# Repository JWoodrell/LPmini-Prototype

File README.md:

# LPmini-Prototype

v1.4b - Fixed a few errors in 1.4, changed jumper section to reflect FR5994 launchpad config

v1.4 - MSP430FR5994 board, onboard debugger

v1.3 - thin form 0.5" wide BGA package

v1.2 - added combo castillations and shrunk width

v1.1 - added TItan logo to back of board and a few small changes

v1.0 - initial board version

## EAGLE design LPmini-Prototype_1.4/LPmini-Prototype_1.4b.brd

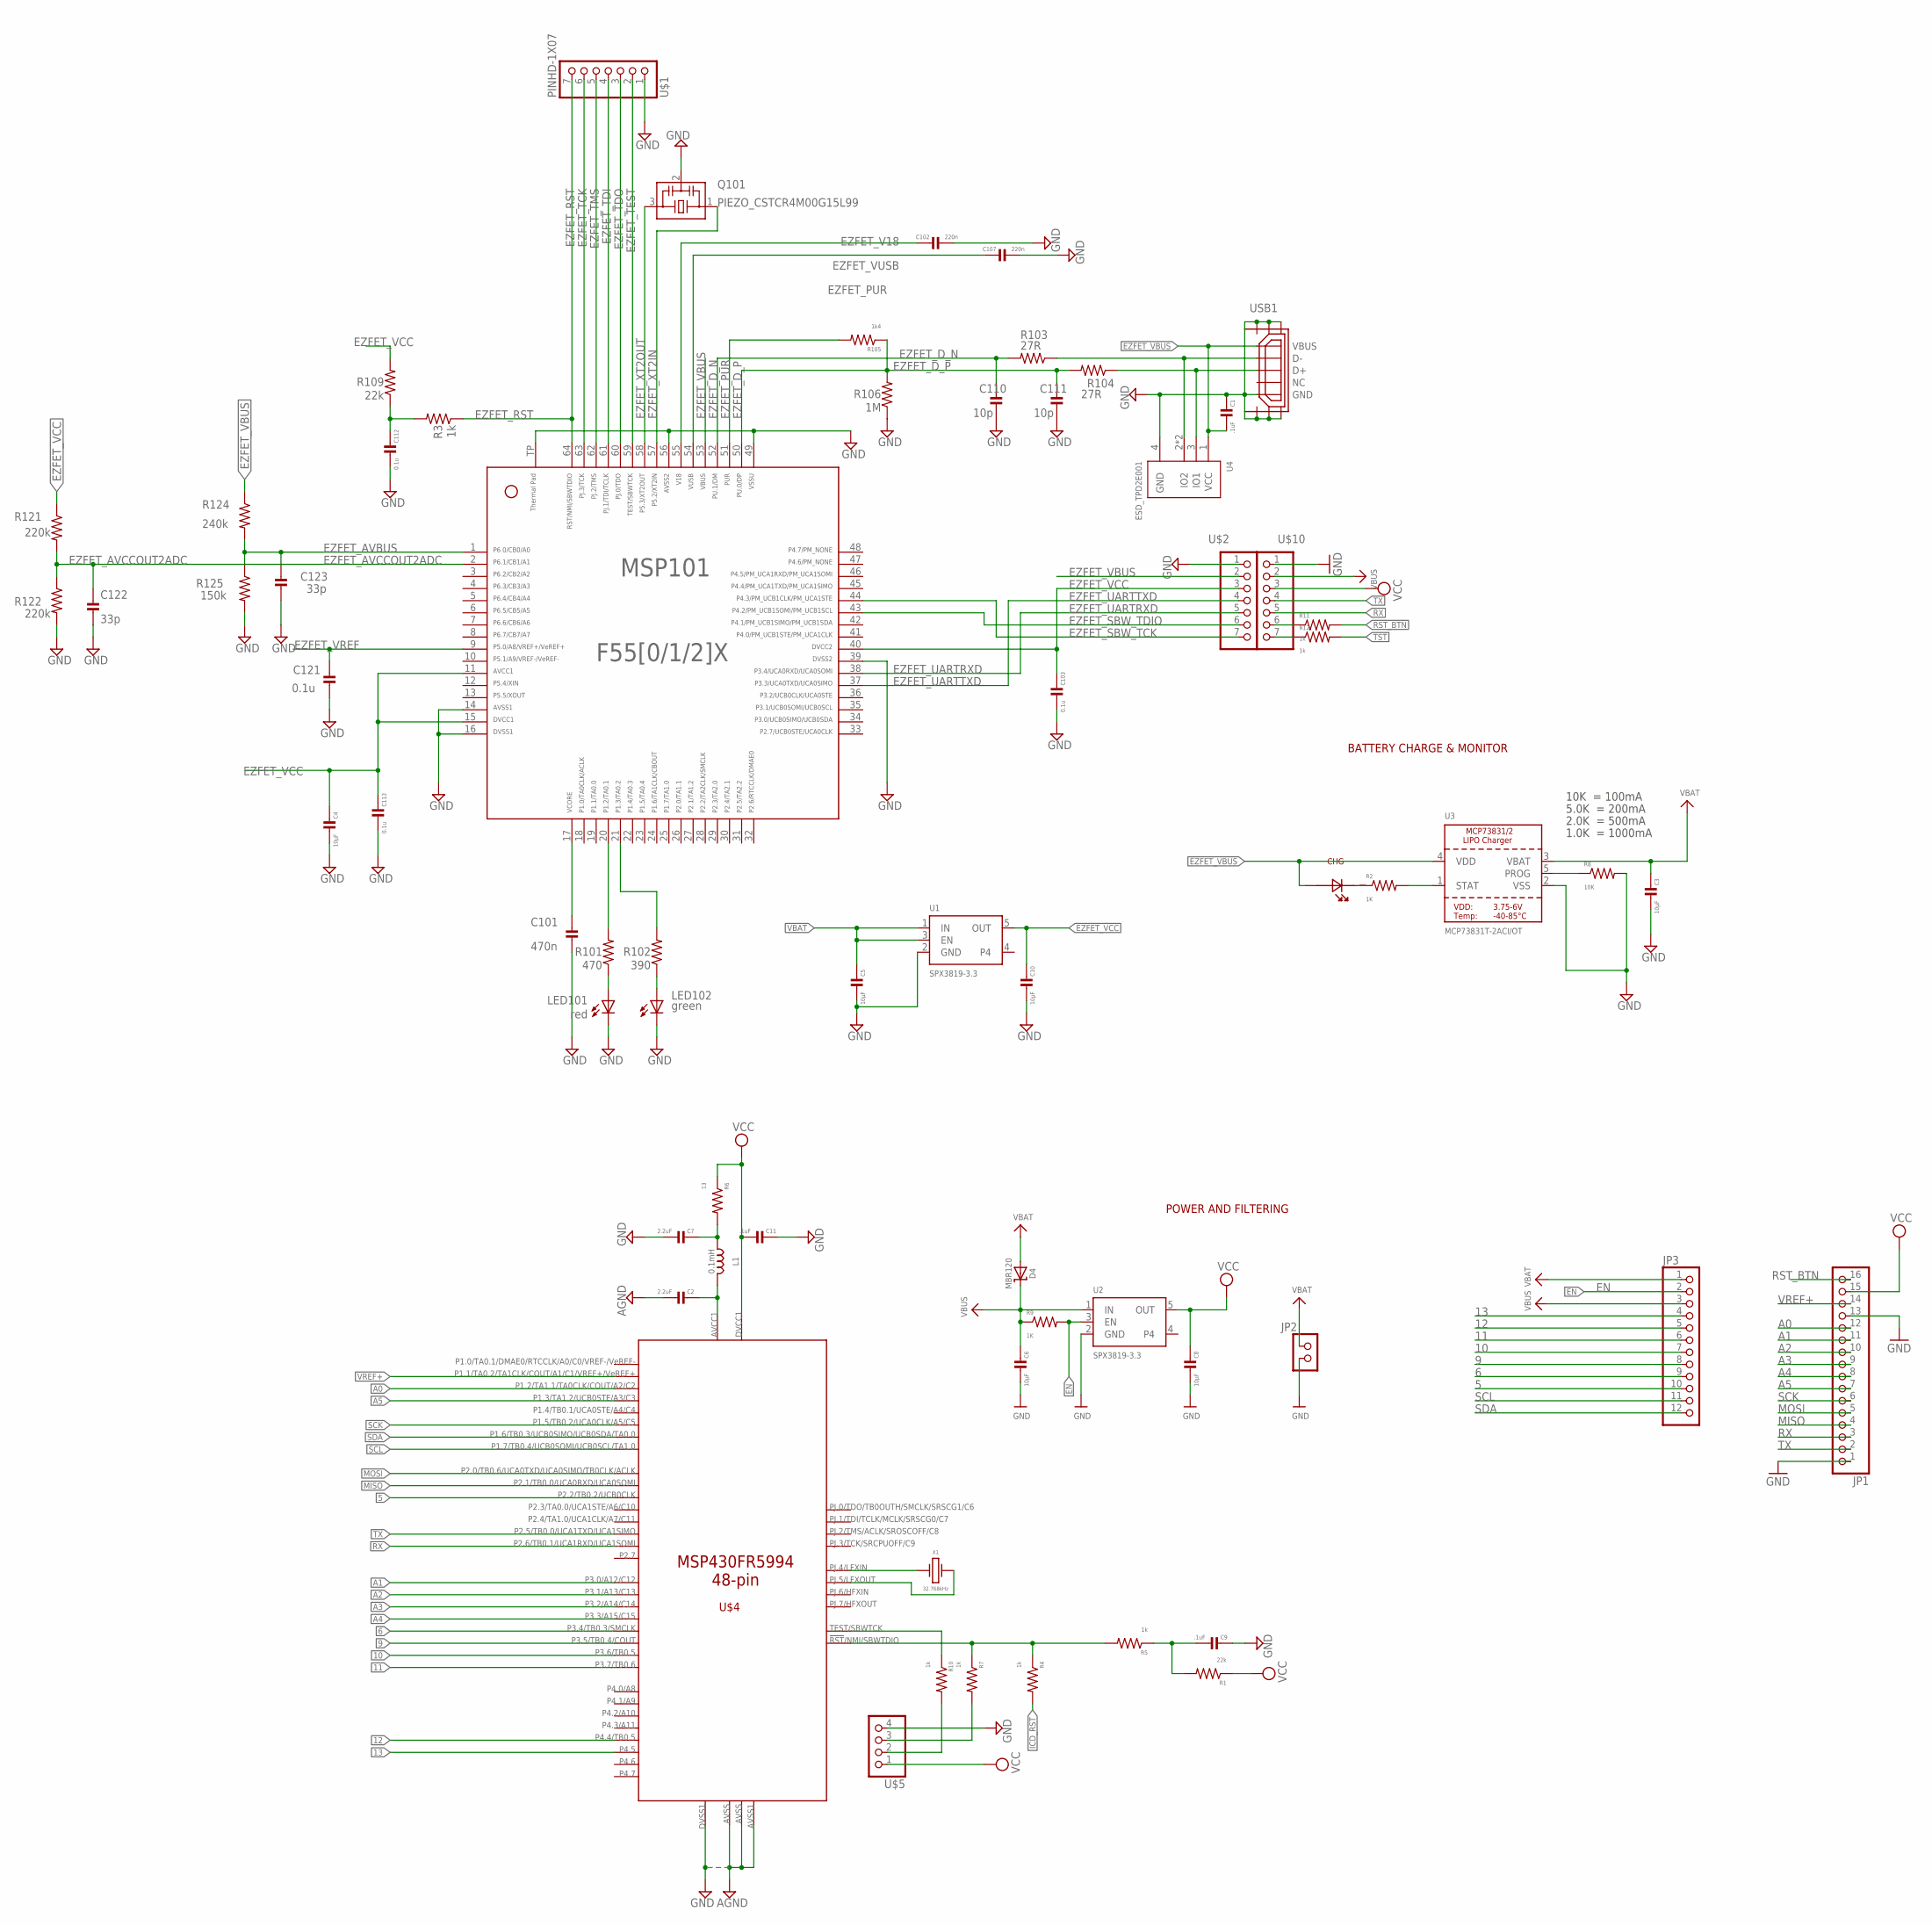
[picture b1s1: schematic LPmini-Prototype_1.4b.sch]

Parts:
C1, C9, C11: .1uF; C0402
C2, C7: 2.2uF; C0603
C3, C4, C5, C6, C8, C10: 10µF; C0603
C101: 470n; C0402
C102, C107: 220n; C0402
C103, C112, C113, C121: 0.1u; C0402
C110, C111: 10p; C0402
C122, C123: 33p; C0402
CHG: ORANGE; LED_0603
D4: MBR120; SOD-123
JP1: HEADER-1X16ROUND; 1X16_ROUND
JP2: 0_JOSEPH_PINHD-1X2END; 0_JOSEPH_1X02-END
JP3: HEADER-1X12; 1X12_ROUND
L1: 0.1mH; RCL_R0805
LED101: red; CHIP-LED0603
LED102: green; CHIP-LED0603
MSP101: MSP430F5528IRGC; RGC64
Q101: PIEZO_CSTCR4M00G15L99; MURATA-FILTER_CSTCR
R1, R109: 22k; R0402
R2, R9: 1K; R0402
R3, R4, R5, R7, R10, R11, R12: 1k; R0402
R6: 13; R0402
R8: 10K; R0402
R101: 470; R0402
R102: 390; R0402
R103, R104: 27R; R0402
R105: 1k4; R0402
R106: 1M; R0402
R121, R122: 220k; R0402
R124: 240k; R0402
R125: 150k; R0402
U1, U2: SPX3819-3.3; SOT23-5
U3: MCP73831T-2ACI/OT; SOT23-5
U4: ESD_TPD2E001; PROJECT7264_TPD2E001-DRL
U$1, U$2, U$10: PINHD-1X07; 1X07
U$4: MSP430FR5994-48PIN; 48QFN
U$5: PINHD_1X4; 1X04
USB1: USB_CON-UPDATE_USB_MICRO_FLIPPED; USB_CON-UPDATE_HIROSE-ZX62R-B-5P
X1: 32.768kHz; CRYSTAL_ABS05

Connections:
5: JP3.10, U$4.26
6: JP3.9, U$4.27
9: JP3.8, U$4.28
10: JP3.7, U$4.29
11: JP3.6, U$4.30
12: JP3.5, U$4.33
13: JP3.4, U$4.34
A0: JP1.12, U$4.3
A1: JP1.11, U$4.4
A2: JP1.10, U$4.5
A3: JP1.9, U$4.6
A4: JP1.8, U$4.7
A5: JP1.7, U$4.9
AGND: C2.2, U$4.41, U$4.44, U$4.47
D_N: R103.1, U4.2 (IO2), U4.5 (IO2), USB1.D-
D_P: R104.1, U4.3 (IO1), USB1.D+
EN: JP3.2, R9.2, U2.3 (EN)
EZFET_AVBUS: C123.2, MSP101.1, R124.2, R125.1
EZFET_AVCCOUT2ADC: C122.2, MSP101.2, R121.2, R122.1
EZFET_D_N: C110.1, MSP101.52, R103.2
EZFET_D_P: C111.1, MSP101.50, R104.2, R105.1, R106.2
EZFET_LED0: MSP101.20, R101.2
EZFET_LED1: MSP101.21, R102.2
EZFET_PUR: MSP101.51, R105.2
EZFET_RST: MSP101.64, R3.1, U$1.7
EZFET_SBW_TCK: MSP101.44, U$2.7
EZFET_SBW_TDIO: MSP101.43, U$2.6
EZFET_TCK: MSP101.63, U$1.6
EZFET_TDI: MSP101.61, U$1.4
EZFET_TDO: MSP101.60, U$1.3
EZFET_TEST: MSP101.59, U$1.2
EZFET_TMS: MSP101.62, U$1.5
EZFET_UARTRXD: MSP101.38, U$2.5
EZFET_UARTTXD: MSP101.37, U$2.4
EZFET_V18: C102.1, MSP101.55
EZFET_VBUS: C1.2, CHG.A, MSP101.53, R124.1, U3.4 (VDD), U4.1 (VCC), U$2.2, USB1.VBUS
EZFET_VCC: C4.1, C10.1, C103.1, C113.1, MSP101.11, MSP101.15, MSP101.40, R109.2, R121.1, U1.5 (OUT), U$2.3
EZFET_VREF: C121.1, MSP101.9
EZFET_VUSB: C107.1, MSP101.54
EZFET_XT2IN: MSP101.57, Q101.1
EZFET_XT2OUT: MSP101.58, Q101.3
GND: C1.1, C3.2, C4.2, C5.2, C6.2, C7.2, C8.2, C9.1, C10.2, C11.1, C101.2, C102.2, C103.2, C107.2, C110.2, C111.2, C112.2, C113.2, C121.2, C122.1, C123.1, JP1.1, JP1.13, JP2.2, LED101.C, LED102.C, MSP101.14, MSP101.16, MSP101.39, MSP101.49, MSP101.56, MSP101.TP, Q101.2, R8.2, R106.1, R122.2, R125.2, U1.2 (GND), U2.2 (GND), U3.2 (VSS), U4.4 (GND), U$1.1, U$2.1, U$4.36, U$4.TAB (36), U$5.4, U$10.1, USB1.GND, USB1.SHIELD1, USB1.SHIELD2, USB1.SHIELD3, USB1.SHIELD4, USB1.SHIELD5, USB1.SHIELD6
ICD_RST: R4.2
MISO: JP1.4, U$4.25
MOSI: JP1.5, U$4.24
unnamed: CHG.K (C), R2.1
unnamed: C9.2, R1.2, R5.1
unnamed: R2.2, U3.1 (STAT)
unnamed: R8.1, U3.5 (PROG)
unnamed: U$4.46, X1.P$2
unnamed: R11.1, U$10.6
unnamed: R10.1, U$4.22
unnamed: C112.1, R3.2, R109.1
unnamed: R12.1, U$10.7
unnamed: U$4.45, X1.P$1
unnamed: C2.1, L1.1, U$4.48
unnamed: C7.1, L1.2, R6.2
unnamed: C101.1, MSP101.17
unnamed: LED101.A, R101.1
unnamed: LED102.A, R102.1
RST: R4.1, R5.2, R7.1, U$4.23
RST_BTN: JP1.16, R7.2, R11.2, U$5.3
RX: JP1.3, U$4.21, U$10.5
SCK: JP1.6, U$4.11
SCL: JP3.11, U$4.32
SDA: JP3.12, U$4.31
TST: R10.2, R12.2, U$5.2
TX: JP1.2, U$4.20, U$10.4
VBAT: C3.1, C5.1, D4.A, JP2.1, JP3.1, U1.1 (IN), U1.3 (EN), U3.3 (VBAT)
VBUS: C6.1, D4.C, JP3.3, R9.1, U2.1 (IN), U$10.2
VCC: C8.1, C11.2, JP1.15, R1.1, R6.1, U2.5 (OUT), U$4.37, U$5.1, U$10.3
VREF+: JP1.14, U$4.2

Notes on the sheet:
POWER AND FILTERING
10K = 100mA
5.0K = 200mA
2.0K = 500mA
1.0K = 1000mA
BATTERY CHARGE & MONITOR

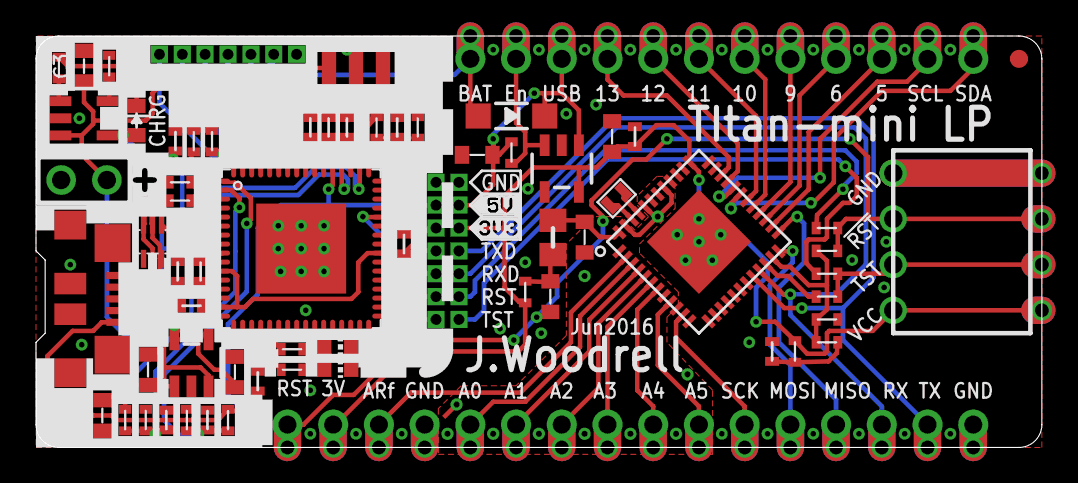
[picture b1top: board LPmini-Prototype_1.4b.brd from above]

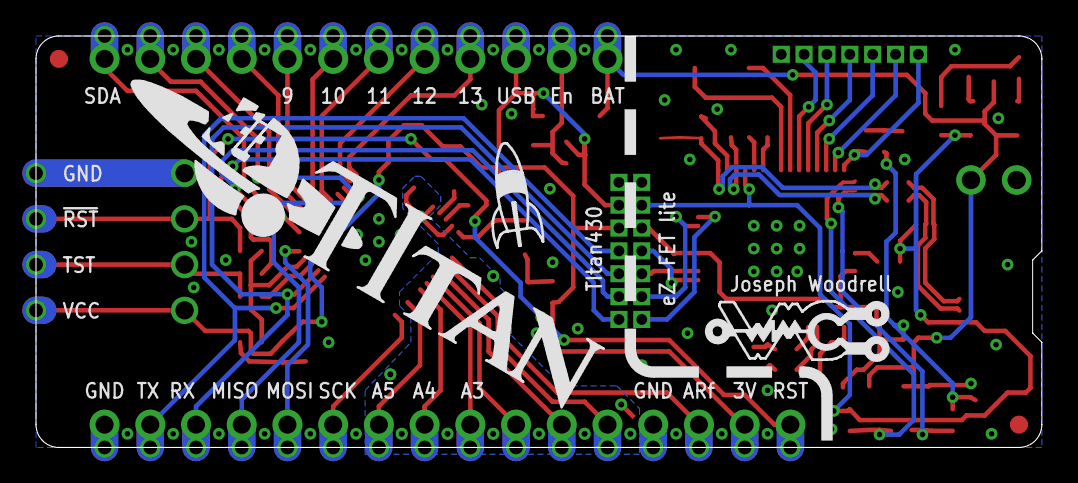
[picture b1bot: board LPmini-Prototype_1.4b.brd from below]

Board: 2 copper layers, 55.9 x 22.9 mm, 71 parts (3 on the bottom side), 71 nets.

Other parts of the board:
U$7: TITAN_LOGO
U$8, U$9: FIDUCIAL
U$11: WMC_LOGO_400MILWIDE
U$13: TI_ROCKET

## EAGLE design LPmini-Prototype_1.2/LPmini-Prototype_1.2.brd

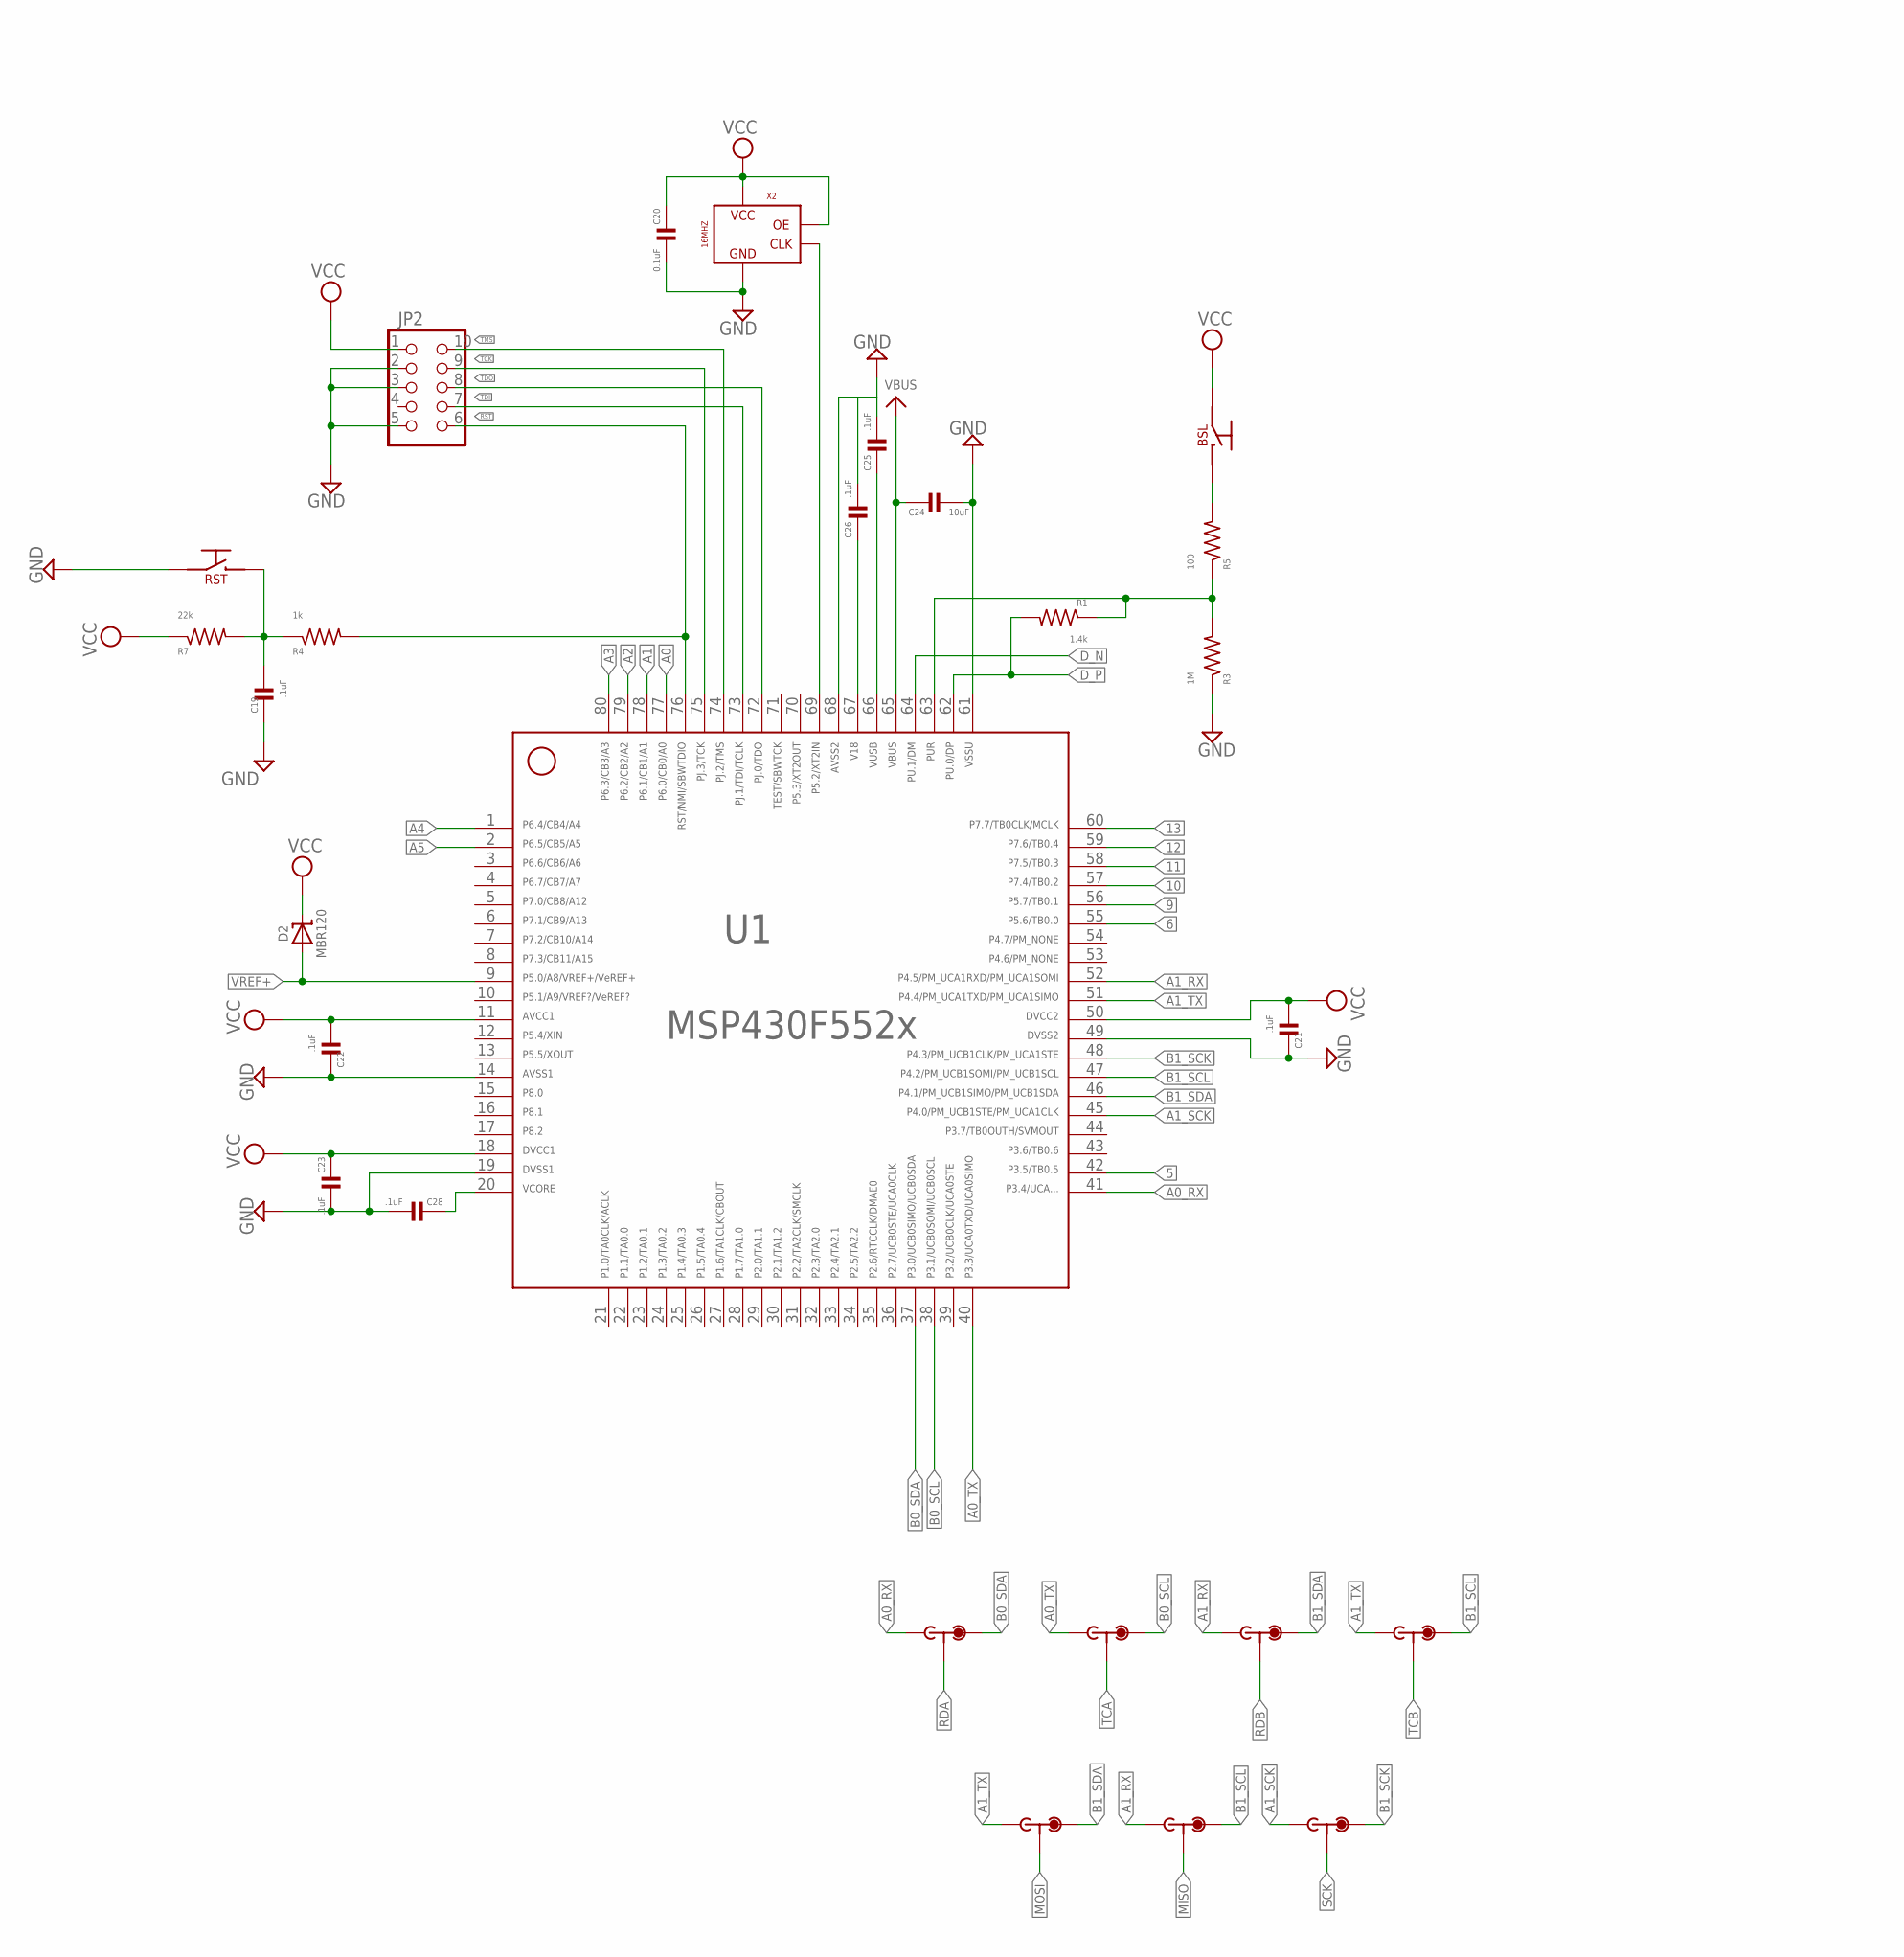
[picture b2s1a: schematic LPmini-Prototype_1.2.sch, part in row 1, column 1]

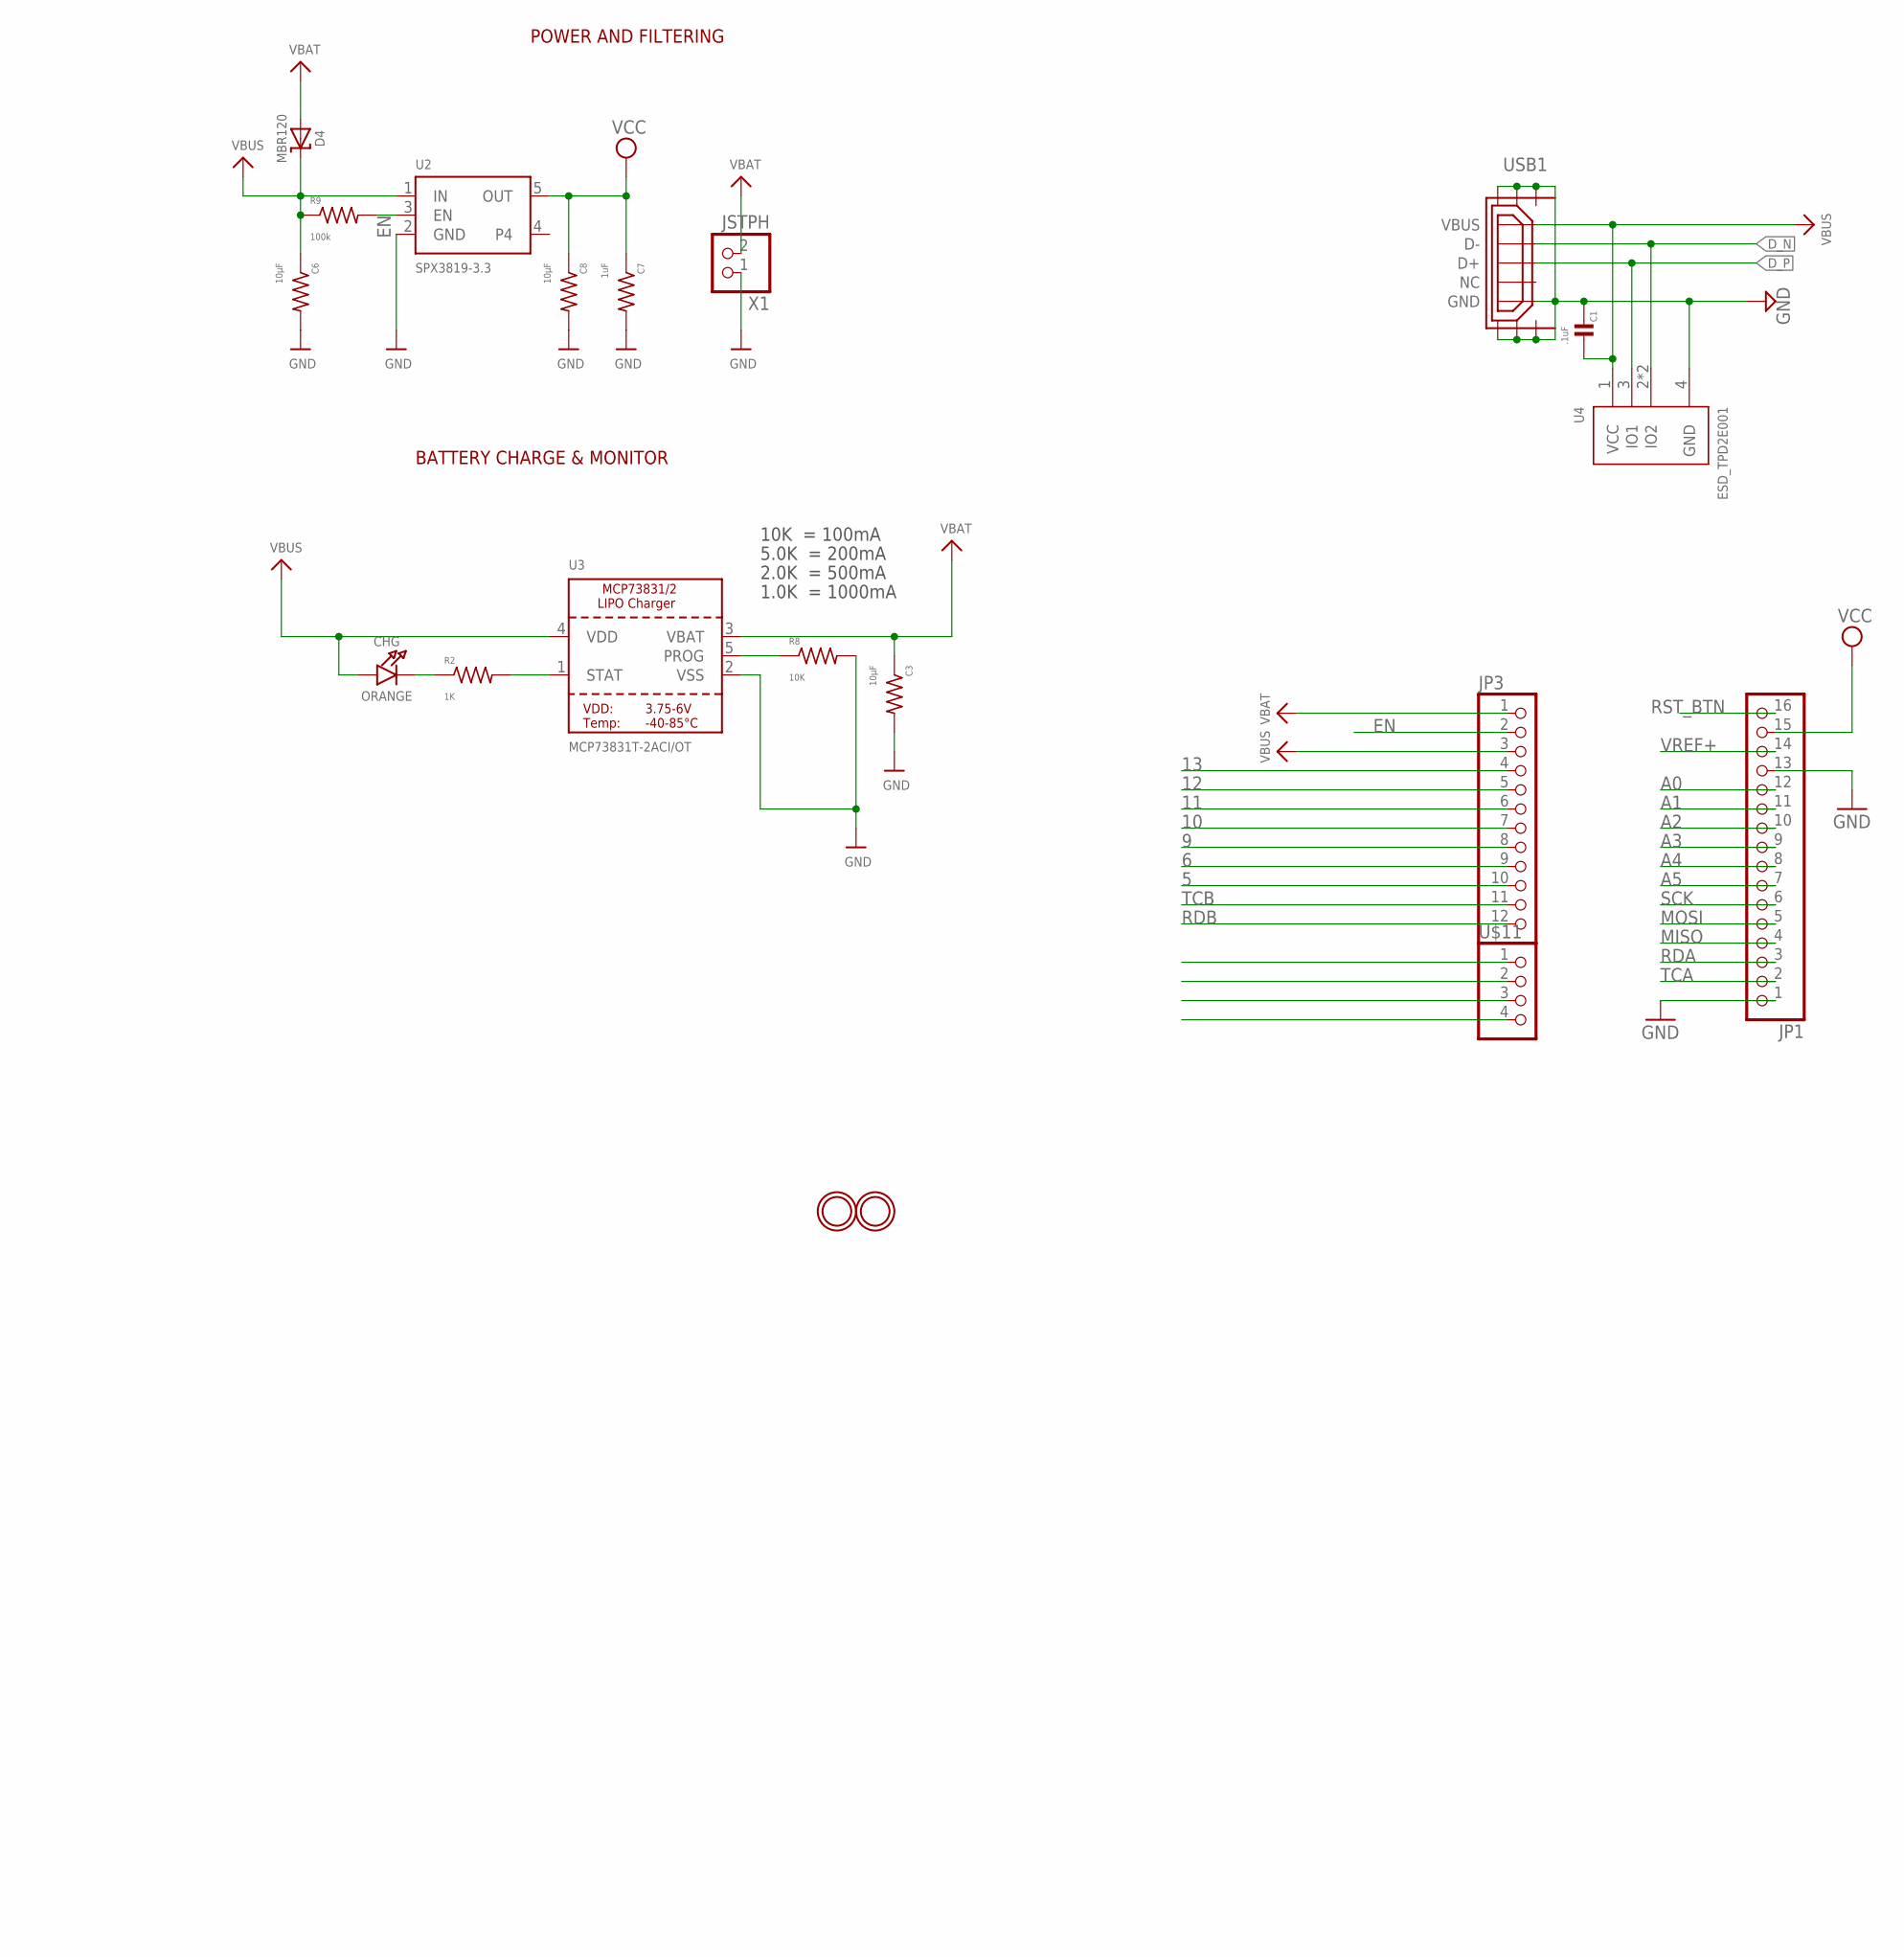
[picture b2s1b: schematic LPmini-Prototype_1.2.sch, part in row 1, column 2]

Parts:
BSL: PB_SMALL_SMD; PB_KMR2
C1, C19, C21, C22, C23, C25, C26, C28: .1uF; C0402
C3, C6, C8: 10µF; R0603
C7: 1uF; R0402
C20: 0.1uF; C0402
C24: 10uF; C0603
CHG: ORANGE; CHIPLED_0805_NOOUTLINE
D2, D4: MBR120; SOD-123
JP1: HEADER-1X16ROUND; 1X16_ROUND
JP2: PINHD_2X05SMD; 2X05-SMALL_SMD
JP3: HEADER-1X12; 1X12_ROUND
R1: 1.4k; R0402
R2: 1K; R0402
R3: 1M; R0402
R4: 1k; R0402
R5: 100; R0402
R7: 22k; R0402
R8: 10K; R0402
R9: 100k; R0402
RST: PB_SMALL_SMD; PB_KMR2
U1: TI_MSP430_V16_INTERN_F552X---PN80; TI_MSP430_V16_INTERN_PN80
U2: SPX3819-3.3; SOT23-5
U3: MCP73831T-2ACI/OT; SOT23-5
U4: ESD_TPD2E001; PROJECT7264_TPD2E001-DRL
U$2, U$4, U$5, U$6, U$8, U$9, U$10: 3PT_SOLDER_JUMPER; SOLDER_JUMPER_3
U$11: PINHD_1X4; 1X04
U$31, U$32: MOUNTINGHOLE2.5; MOUNTINGHOLE_2.5_PLATED
USB1: USB_CON-UPDATE_USB_MICRO_FLIPPED; USB_CON-UPDATE_HIROSE-ZX62R-B-5P
X1: JSTPH; JSTPH2
X2: 16MHZ; OSCILLATOR_3.3X2.6

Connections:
5: JP3.10, U1.42
6: JP3.9, U1.55
9: JP3.8, U1.56
10: JP3.7, U1.57
11: JP3.6, U1.58
12: JP3.5, U1.59
13: JP3.4, U1.60
A0: JP1.12, U1.77
A0_RX: U1.41, U$2.2 (NO)
A0_TX: U1.40, U$8.2 (NO)
A1: JP1.11, U1.78
A1_RX: U1.52, U$5.2 (NO), U$9.2 (NO)
A1_SCK: U1.45, U$6.2 (NO)
A1_TX: U1.51, U$4.2 (NO), U$10.2 (NO)
A2: JP1.10, U1.79
A3: JP1.9, U1.80
A4: JP1.8, U1.1
A5: JP1.7, U1.2
B0_SCL: U1.38, U$8.1 (NC)
B0_SDA: U1.37, U$2.1 (NC)
B1_SCK: U1.48, U$6.1 (NC)
B1_SCL: U1.47, U$5.1 (NC), U$10.1 (NC)
B1_SDA: U1.46, U$4.1 (NC), U$9.1 (NC)
D_N: U1.64, U4.2 (IO2), U4.5 (IO2), USB1.D-
D_P: R1.2, U1.62, U4.3 (IO1), USB1.D+
EN: JP3.2, R9.2, U2.3 (EN)
GND: C1.2, C3.2, C6.2, C7.2, C8.2, C19.2, C20.2, C21.2, C22.2, C23.2, C24.2, C25.2, C26.2, C28.2, JP1.1, JP1.13, JP2.2, JP2.3, JP2.5, R3.1, R8.2, RST.1A (A), RST.1B (A), U1.14, U1.19, U1.49, U1.61, U1.68, U2.2 (GND), U3.2 (VSS), U4.4 (GND), USB1.GND, USB1.SHIELD1, USB1.SHIELD2, USB1.SHIELD3, USB1.SHIELD4, USB1.SHIELD5, USB1.SHIELD6, X1.1, X2.2
MISO: JP1.4, U$5.C (IN)
MOSI: JP1.5, U$4.C (IN)
unnamed: CHG.C, R2.1
unnamed: R2.2, U3.1 (STAT)
unnamed: R8.1, U3.5 (PROG)
unnamed: BSL.2A (B), BSL.2B (B), R5.2
unnamed: R1.1, R3.2, R5.1, U1.63
unnamed: C25.1, U1.66
unnamed: C26.1, U1.67
unnamed: C28.1, U1.20
unnamed: U1.69, X2.3
RDA: JP1.3, U$2.C (IN)
RDB: JP3.12, U$9.C (IN)
RST: JP2.6, R4.2, U1.76
RST_BTN: C19.1, JP1.16, R4.1, R7.2, RST.2A (B), RST.2B (B)
SCK: JP1.6, U$6.C (IN)
TCA: JP1.2, U$8.C (IN)
TCB: JP3.11, U$10.C (IN)
TCK: JP2.9, U1.75
TDI: JP2.7, U1.73
TDO: JP2.8, U1.72
TMS: JP2.10, U1.74
VBAT: C3.1, D4.A, JP3.1, U3.3 (VBAT), X1.2
VBUS: C1.1, C6.1, C24.1, CHG.A, D4.C, JP3.3, R9.1, U1.65, U2.1 (IN), U3.4 (VDD), U4.1 (VCC), USB1.VBUS
VCC: BSL.1A (A), BSL.1B (A), C7.1, C8.1, C20.1, C21.1, C22.1, C23.1, D2.C, JP1.15, JP2.1, R7.1, U1.11, U1.18, U1.50, U2.5 (OUT), X2.1, X2.4
VREF+: D2.A, JP1.14, U1.9

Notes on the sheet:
POWER AND FILTERING
10K = 100mA
5.0K = 200mA
2.0K = 500mA
1.0K = 1000mA
BATTERY CHARGE & MONITOR

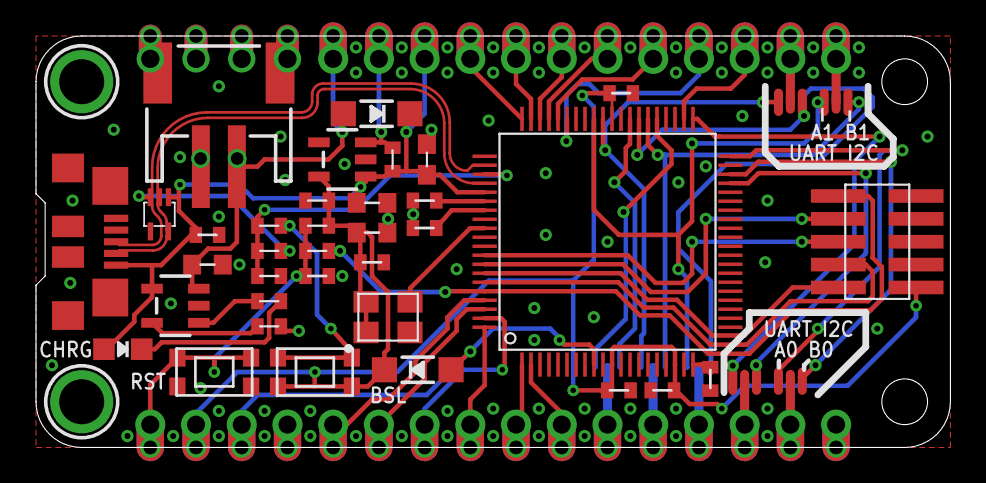
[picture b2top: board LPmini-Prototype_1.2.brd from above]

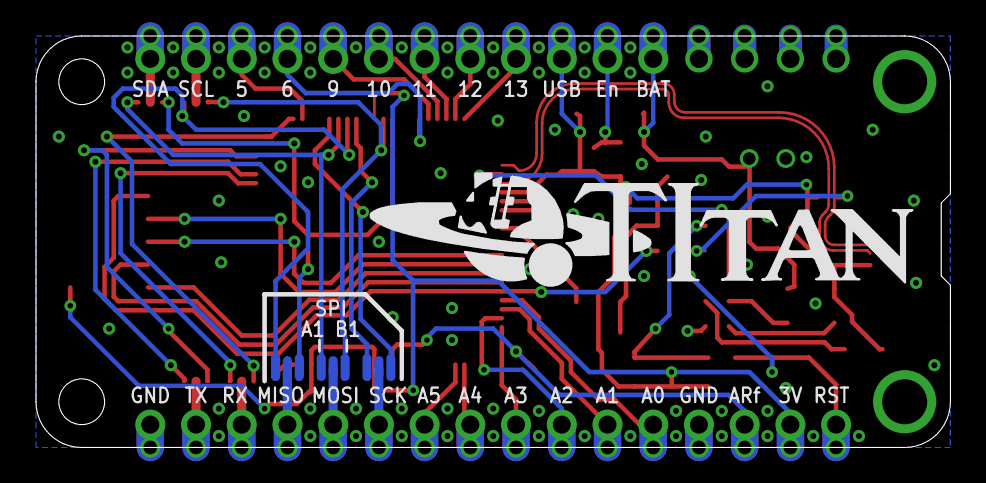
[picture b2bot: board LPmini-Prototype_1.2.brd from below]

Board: 2 copper layers, 50.8 x 22.9 mm, 48 parts (4 on the bottom side), 53 nets.

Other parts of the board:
U$7: TITAN_LOGO

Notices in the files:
parts and their libraries:
microbuilder: This work is placed in the public domain, and may be freely used for commercial and non-commercial work with the following conditions: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
